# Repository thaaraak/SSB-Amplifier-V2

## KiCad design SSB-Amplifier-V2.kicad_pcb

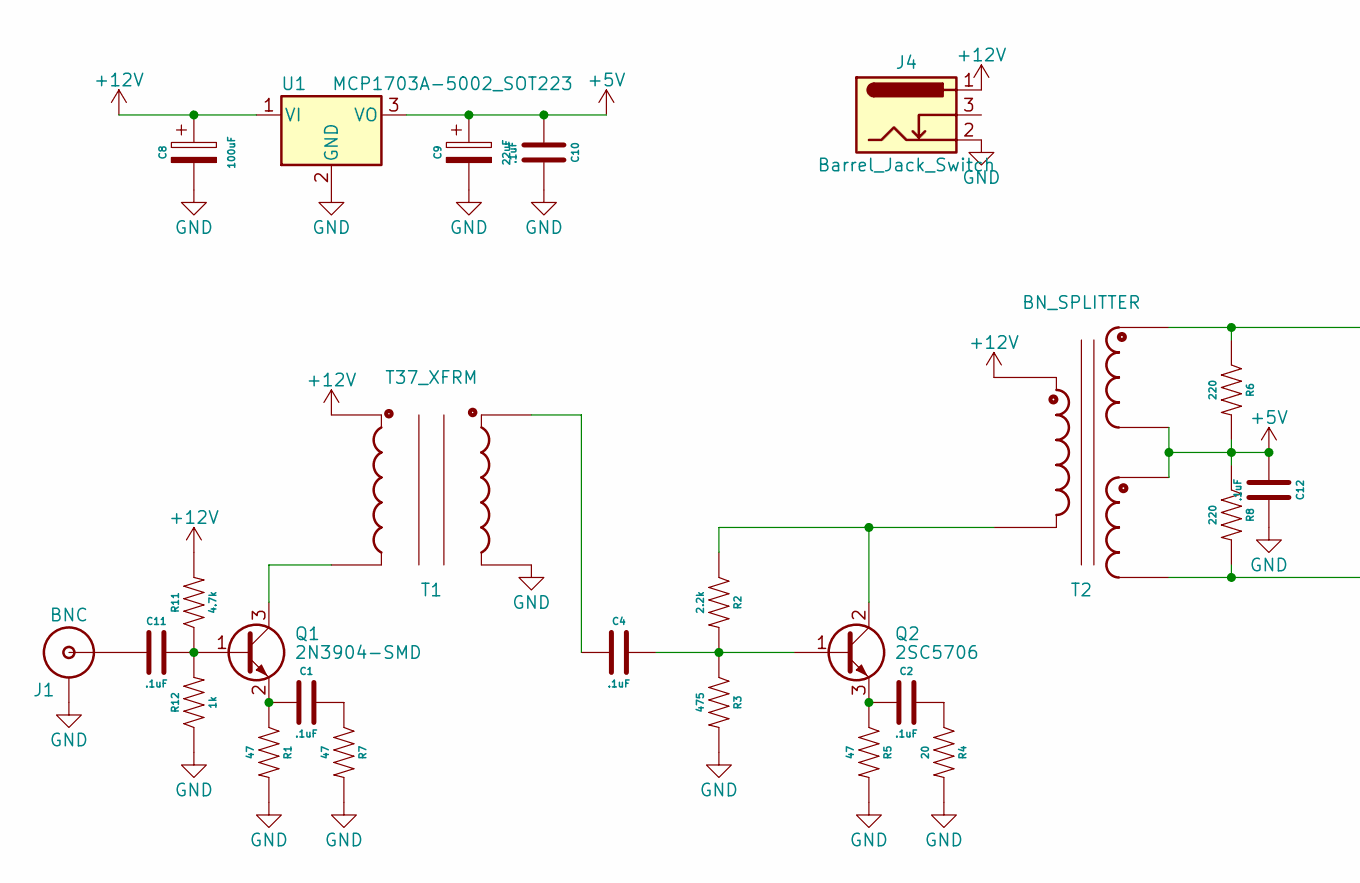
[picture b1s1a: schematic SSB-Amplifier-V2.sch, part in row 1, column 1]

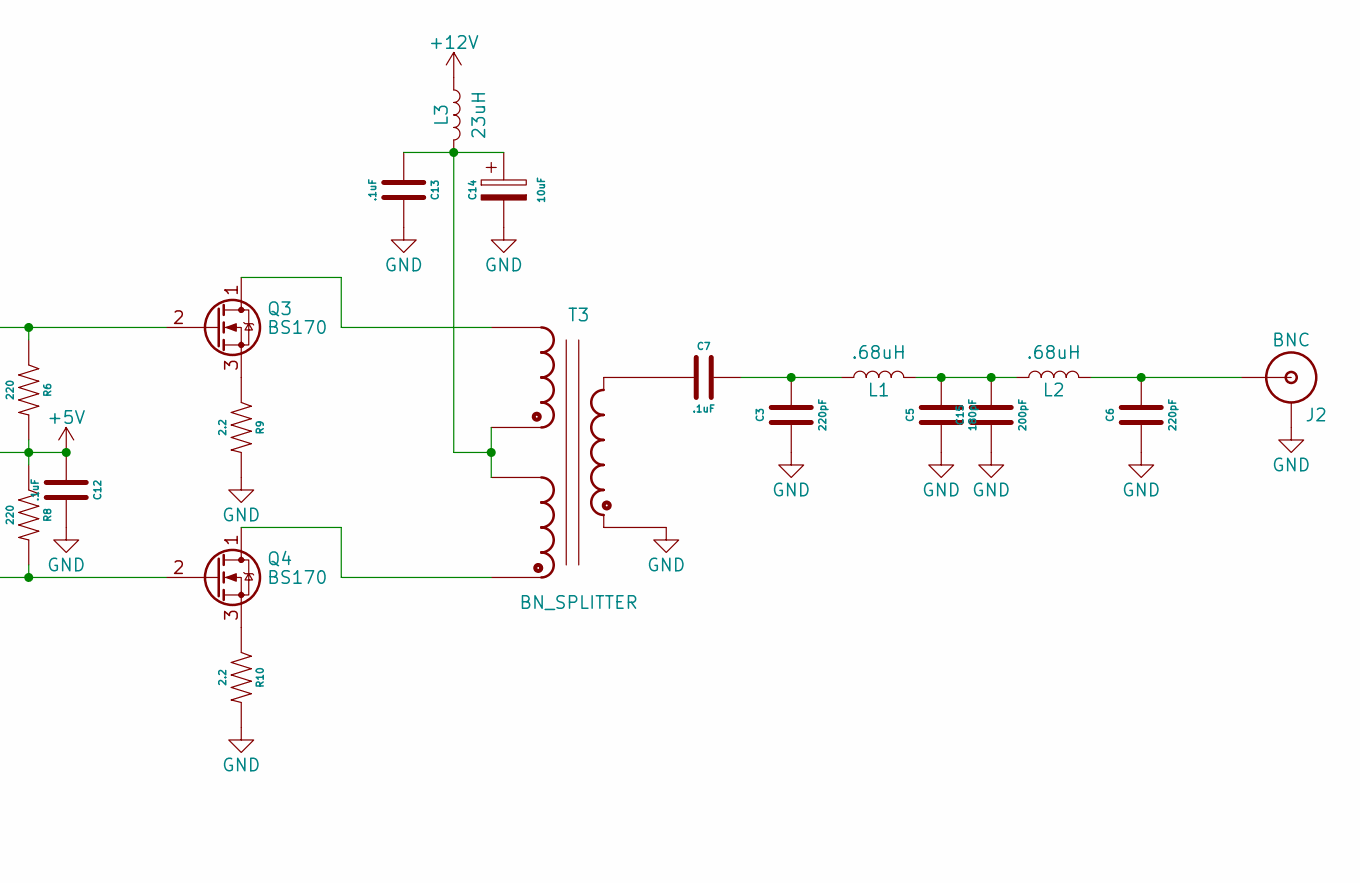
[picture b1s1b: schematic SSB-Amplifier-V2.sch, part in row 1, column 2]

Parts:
C1, C2, C4, C7, C10, C11, C12, C13: .1uF; Capacitor 0805
C3, C6: 220pF; Capacitor 0805
C5: 180pF; Capacitor 0805
C8: 100uF; CP_Elec_6.3x5.4
C9: 22uF; CP_Elec_4x5.4
C14: 10uF; CP_Elec_4x5.4
C15: 200pF; Capacitor 0805
J1, J2: BNC
J4: Barrel_Jack_Switch; BarrelJack_Horizontal
L1, L2: .68uH; T37_Inductor
L3: 23uH; BN-43-2402
Q1: 2N3904-SMD; SOT-23
Q2: 2SC5706; TO-252-2
Q3, Q4: BS170; TO-92_Inline_Wide
R1, R5, R7: 47; Resistor 0805
R2: 2.2k; Resistor 0805
R3: 475; Resistor 0805
R4: 20; Resistor 0805
R6, R8: 220; Resistor 0805
R9, R10: 2.2; Resistor 1206
R11: 4.7k; Resistor 0805
R12: 1k; Resistor 0805
T1: T37_XFRM; T37 Transformer
T2, T3: BN_SPLITTER; BN-302-Splitter
U1: MCP1703A-5002_SOT223; TO-252-3_TabPin2

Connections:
+5V: C9.1, C10.1, C12.1, R6.2, R8.1, T2.C2B, T2.C3A, U1.3 (VO)
+12V: C8.1, J4.1, L3.1, R11.2, T1.C1B, T2.C1A, U1.1 (VI)
GND: C3.1, C5.1, C6.1, C8.2, C9.2, C10.2, C12.2, C13.2, C14.2, C15.1, J1.GND, J2.GND, J4.2, R1.2, R3.2, R4.2, R5.2, R7.2, R9.2, R10.2, R12.1, T1.C2A, T3.C1A, U1.2 (GND)
unnamed: C1.1, Q1.2 (E), R1.1
unnamed: C1.2, R7.1
unnamed: C2.1, Q2.3 (E), R5.1
unnamed: C2.2, R4.1
unnamed: C3.2, C7.2, L1.1
unnamed: C4.1, T1.C2B
unnamed: C4.2, Q2.1 (B), R2.2, R3.1
unnamed: C6.2, J2.S (OUT), L2.2
unnamed: C7.1, T3.C1B
unnamed: C11.1, J1.S (OUT)
unnamed: C11.2, Q1.1 (B), R11.1, R12.2
unnamed: C13.1, C14.1, L3.2, T3.C2B, T3.C3A
unnamed: C5.2, C15.2, L1.2, L2.1
unnamed: Q1.3 (C), T1.C1A
unnamed: Q2.2 (C), R2.1, T2.C1B
unnamed: Q3.1 (D), T3.C3B
unnamed: Q3.2 (G), R6.1, T2.C2A
unnamed: Q3.3 (S), R9.1
unnamed: Q4.1 (D), T3.C2A
unnamed: Q4.2 (G), R8.2, T2.C3B
unnamed: Q4.3 (S), R10.1

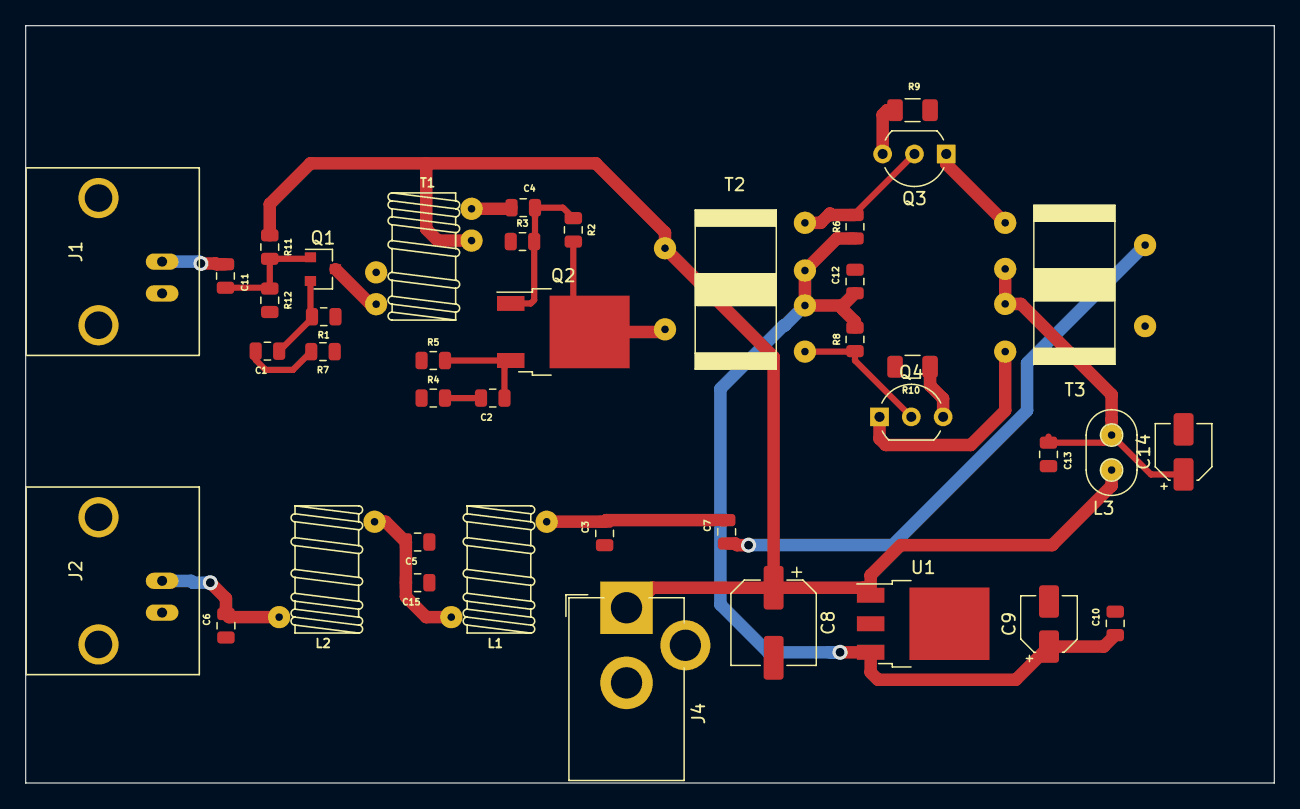
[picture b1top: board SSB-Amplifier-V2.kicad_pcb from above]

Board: 2 copper layers, 99.8 x 60.5 mm, 41 parts (0 on the bottom side), 24 nets.

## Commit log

2020-10-04 adding pdf
